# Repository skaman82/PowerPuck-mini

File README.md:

# PowerPuck-mini
2S Li-Ion power system for FPV goggles (allows the use of full capacity potential of li-ion cells). This is the second version whitch is much easier to build compaired to V1 (and is also much smaller).

# Features:
• 9V Step-Up from a 2S source <br>
• On/off button<br>
• Adjustable low-voltage alarm<br>
• LED power and capacity indicator<br>

# PARTS:
Notes: Voltage divider is currently designed for 10v max. <br>

## PCB
C1,C5: 		100nF C0603 Capacitor (2x)<br>
C2: 		10nF C0805 Capacitor (1x)<br>
C3: 		1uF C0805 Capacitor 25V (1x)<br>
C4: 		2.2uF C0805 Capacitor (1x)<br>
LS1: 		Speaker CSS-0575B-SMT (1x)<br>
Q1, Q2:		BC848 30V 100mA SOT23-3 Transistor (2x)<br>
Q3: 		IRLML6402 Power Mosfet (1x)<br>
R8, R9:	  5k6 R0603 Resistor (2x)<br>
R7, R5: 		10k R0603 Resistor (2x)<br>
S1: 		MOMENTARY-SWITCH SMD 5.2MM (1x)<br>
U1: 		WS2812-2020 LED (1x)<br>
U2: 		LP2985 5V LDO Reg (1x)<br>
•: 		ATTINY85 SOIC8 (1x)<br><br>

## Additional
+ Produced PCB (0.8-1mm thicknes required for the case)<br>
+ U3V12F9		Pololu 9V Step-Up<br>
+ Printed case parts (use PETG because of the heat from the step-up. TPU for the relief)<br>
+ ISP flashing tool (and SOIC8 clamp) like USBTinyISP<br>
+ 1.5m 5.5 x 2.1 DC cable like this: https://www.ebay.de/itm/0-50-1-00-1-50-m-USB-DC-Kabel-5-5-x-2-1-2-5-mm-Winkelstecker-CU-15855/293148509182 (cut the USB and replace it with your own connector)<br>
+ 2S li-ion battery pack. 3500mah 18650 will last about 3.5h, 5000mah 21700 will last about 5h. 18650 DIY battery case see the V1: https://github.com/skaman82/PowerPuck<br>

# ASSEMBLY
+ Solder all the SMD parts and the step-up to the PCB
+ Compile and flash the code with ArduinoIDE using an ISP programmer (use the right hardware package mentioned in the code)
+ Connect to a 2S power source and test if everything is working
+ Solder on the cables, put it in the pinted case and glue it together

# OPERATION
Connect the battery. The device is powered on and the LED is showing the battery status as follows: <br>
+ GREEN: voltage is 4.20 - 3.65v per cell (full)<br>
+ YELLOW: voltage is 3.64- 3.45v per cell (half)<br>
+ RED: voltage is 3.44 - alarmvoltage (one third)<br>
+ BLINKING RED and beeping: voltage is below alarm voltage<br>
<br>
- Press the button once to toggle between ON and OFF state.<br>
- Press the button for 2 sek. to enter the setup-menu<br>
<br>
SETUP MENU:<br>
Press the button to toggle between settings:<br>

• GREEN: voltage alarm at 3.35v per cell<br>
• YELLOW: voltage alarm at 3.25v per cell<br>
• RED: voltage alarm at at 3.15v per cell<br>
- Press the button for 2 sek. to save your alarm setting and exit the setup menu <br>

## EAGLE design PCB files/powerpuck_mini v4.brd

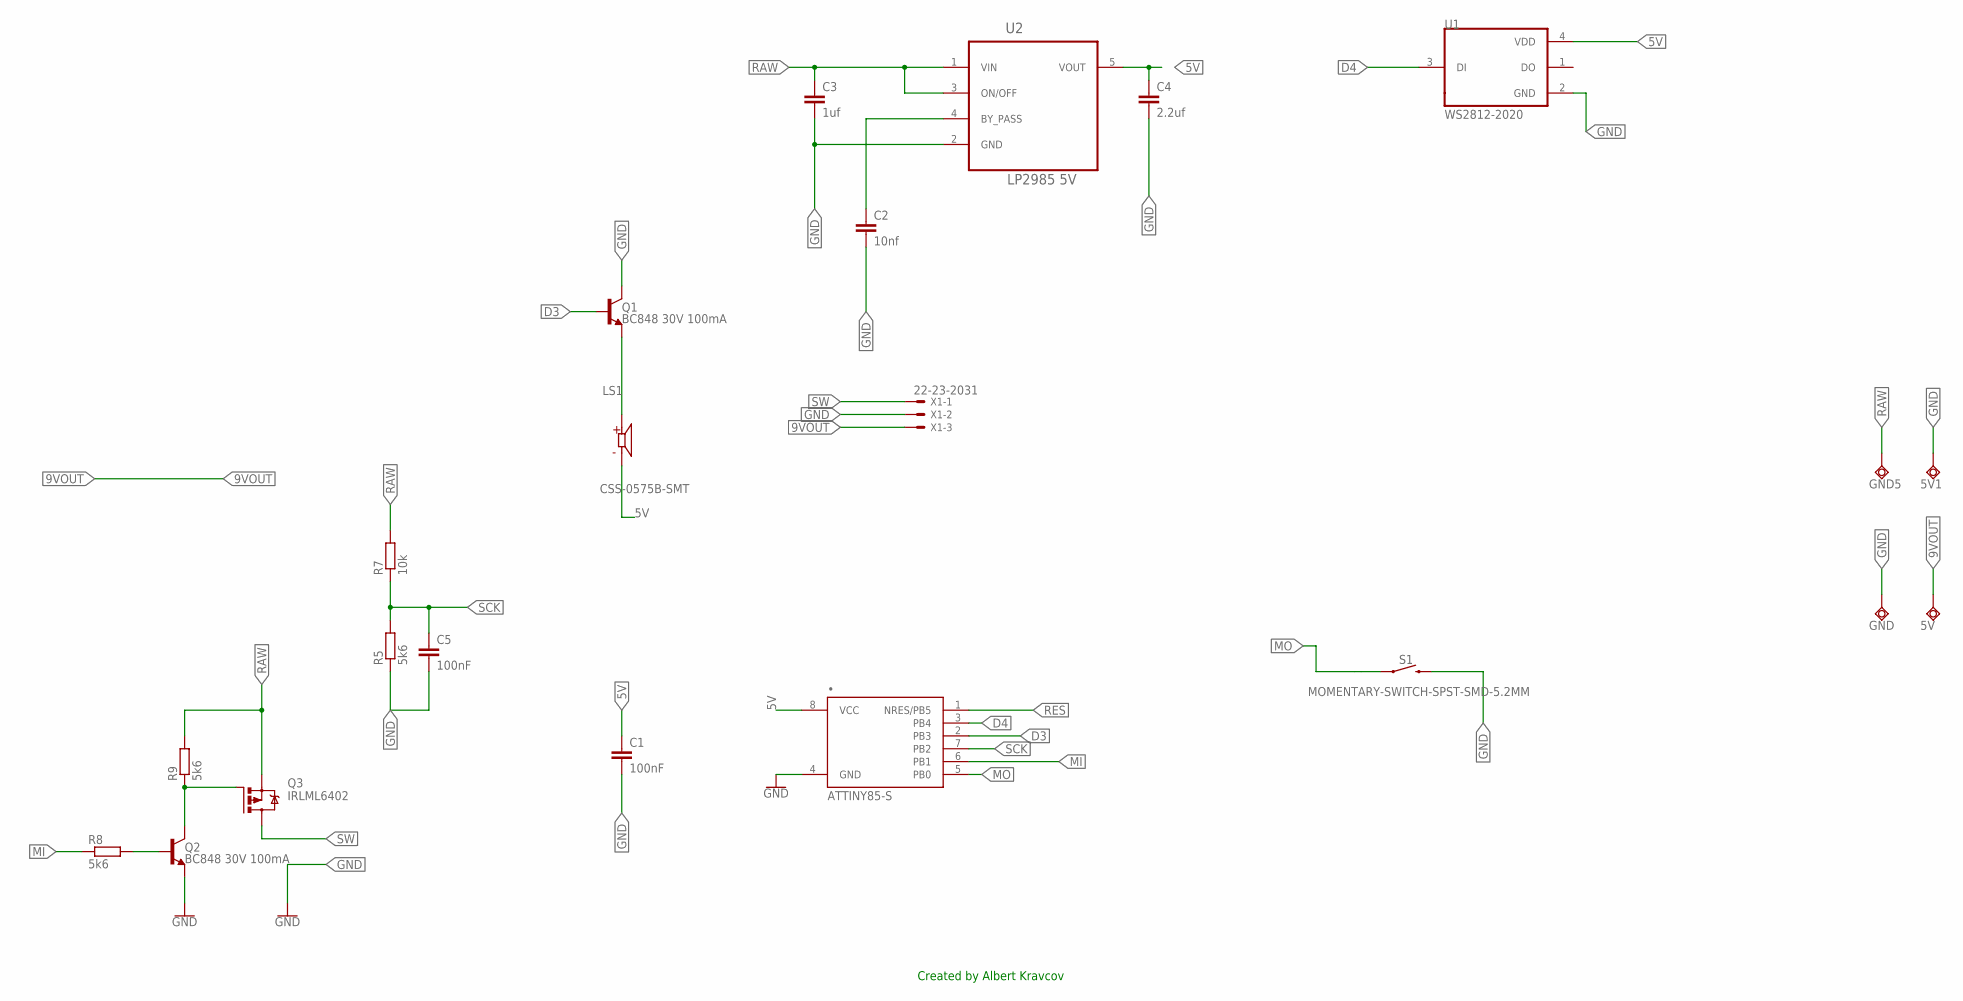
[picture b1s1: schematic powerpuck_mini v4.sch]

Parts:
5V, 5V1: TPSQTP20R; TP20R
C1, C5: 100nF; C0603
C2: 10nf; C0805
C3: 1uf; C0805
C4: 2.2uf; C0805
GND, GND5: TPSQTP20R; TP20R
LS1: CSS-0575B-SMT; CUI_CSS-0575B-SMT
Q1, Q2: BC848 30V 100mA; SOT23-3
Q3: IRLML6402; MICRO3
R5, R8, R9: 5k6; R0603
R7: 10k; R0603
S1: MOMENTARY-SWITCH-SPST-SMD-5.2MM; TACTILE_SWITCH_SMD_5.2MM
U1: WS2812-2020; LED_WS2812-2020
U2: LP2985 5V; SOT95P284X119-5N
X1: 22-23-2031
•: ATTINY85-S; SOIC8_EIAJ_208MIL

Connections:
5V: C1.1, C4.1, LS1.2 (N), U1.4 (VDD), U2.5 (VOUT), •.8 (VCC)
9VOUT: 5V.TP, X1.3
D3: Q1.1 (B), •.2 (PB3)
D4: U1.3 (DI), •.3 (PB4)
GND: 5V1.TP, C1.2, C2.2, C3.2, C4.2, C5.2, GND.TP, Q1.3 (C), Q2.2 (E), R5.1, S1.3 (2), U1.2 (GND), U2.2 (GND), X1.2, •.4 (GND)
MI: R8.1, •.6 (PB1)
MO: S1.1, •.5 (PB0)
unnamed: C2.1, U2.4 (BY_PASS)
unnamed: LS1.1, Q1.2 (E)
unnamed: Q2.1 (B), R8.2
unnamed: Q2.3 (C), Q3.1 (G), R9.1
RAW: C3.1, GND5.TP, Q3.2 (S), R7.2, R9.2, U2.1 (VIN), U2.3 (ON/OFF)
RES: •.1 (NRES/PB5)
SCK: C5.1, R5.2, R7.1, •.7 (PB2)
SW: Q3.3 (D), X1.1

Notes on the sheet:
Created by Albert Kravcov

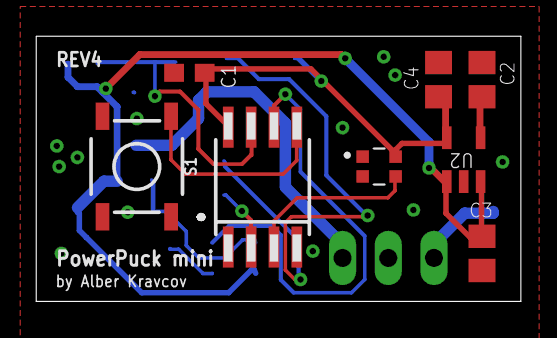
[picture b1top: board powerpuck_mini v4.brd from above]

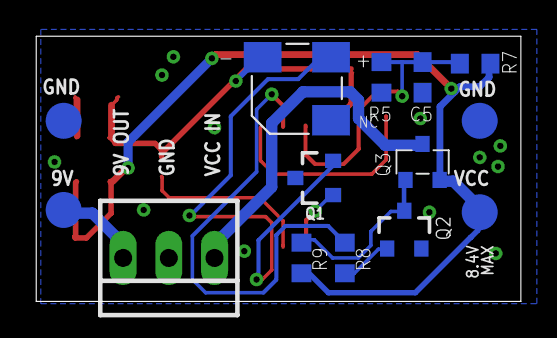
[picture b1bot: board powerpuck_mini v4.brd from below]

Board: 2 copper layers, 26.9 x 14.7 mm, 22 parts (14 on the bottom side), 14 nets.

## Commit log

2020-12-21 initial upload
2020-12-21 adding PCB images

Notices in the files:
parts and their libraries:
SparkFun-DiscreteSemi: Licensing: Creative Commons ShareAlike 4.0 International - https://creativecommons.org/licenses/by-sa/4.0
